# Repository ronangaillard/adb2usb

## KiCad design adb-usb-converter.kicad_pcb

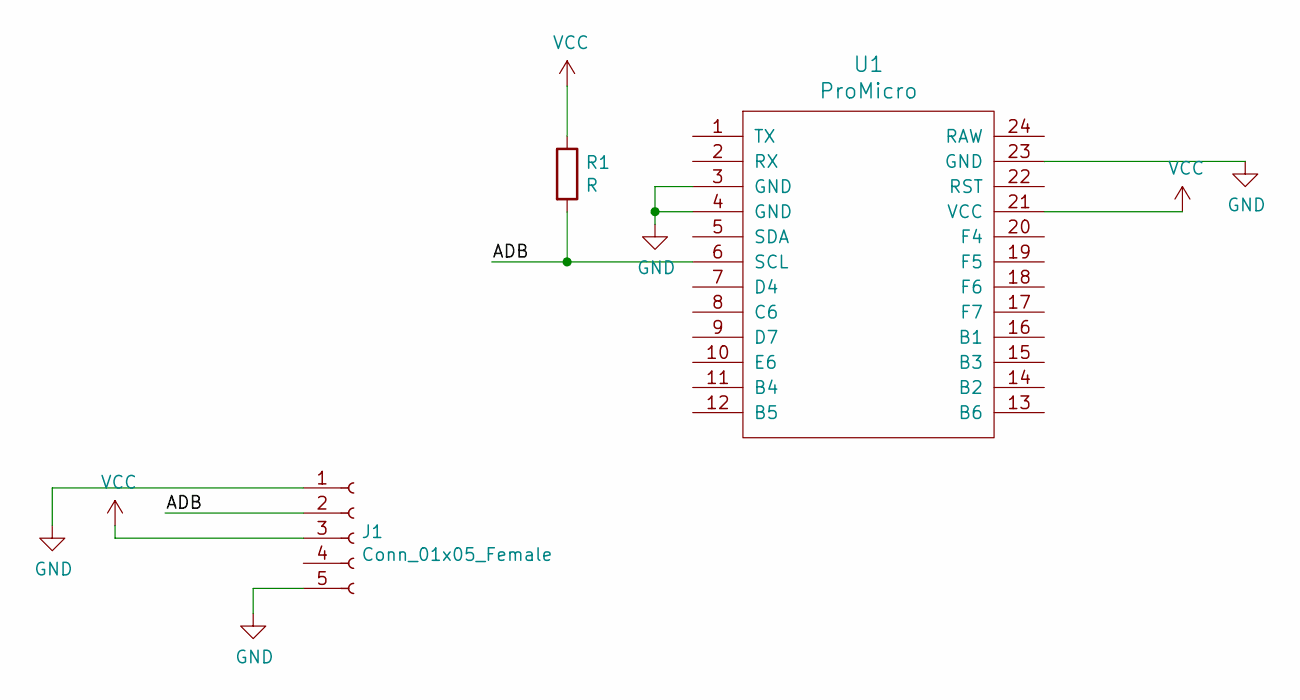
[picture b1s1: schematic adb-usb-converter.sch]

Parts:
J1: Conn_01x05_Female; adb_connector
R1: R; R_Axial_DIN0204_L3.6mm_D1.6mm_P7.62mm_Horizontal
U1: ProMicro; ProMicro-NoSilk

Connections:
/ADB: J1.2, R1.2, U1.6 (SCL)
GND: J1.1, J1.5, U1.3 (GND), U1.4 (GND), U1.23 (GND)
VCC: J1.3, R1.1, U1.21 (VCC)

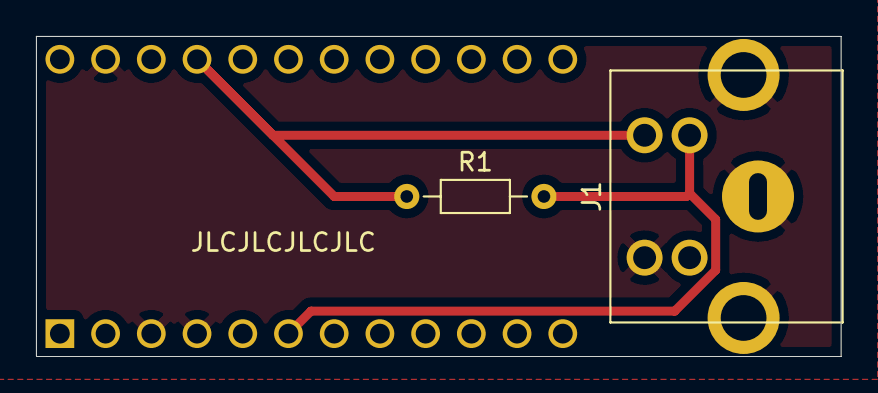
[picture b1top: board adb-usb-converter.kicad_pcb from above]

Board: 2 copper layers, 44.7 x 17.8 mm, 3 parts (0 on the bottom side), 3 nets.
